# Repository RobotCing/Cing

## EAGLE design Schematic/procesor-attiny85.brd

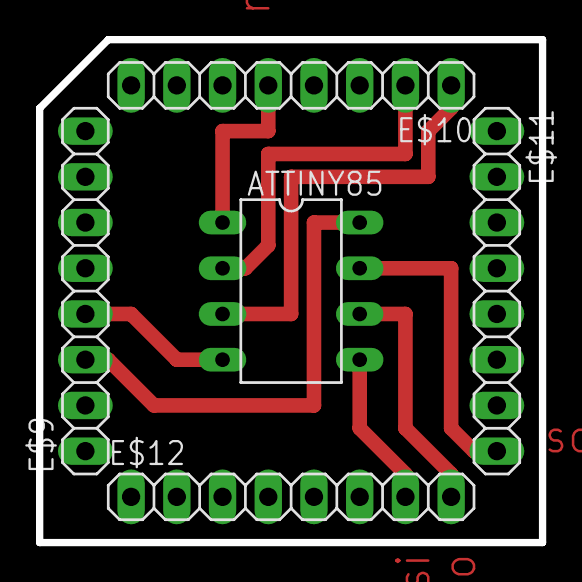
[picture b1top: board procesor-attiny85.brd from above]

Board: 2 copper layers, 27.9 x 27.9 mm, 5 parts (0 on the bottom side), 8 nets.

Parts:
ATTINY85: DIL08
E$9, E$10, E$11, E$12: 1X08

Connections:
S$2: ATTINY85.1, E$10.5
S$3: ATTINY85.4, E$9.4
S$4: ATTINY85.8, E$9.3
S$5: ATTINY85.7, E$11.8
S$6: ATTINY85.3, E$10.1
S$7: ATTINY85.2, E$10.2
S$8: ATTINY85.5, E$12.7
S$10: ATTINY85.6, E$12.8

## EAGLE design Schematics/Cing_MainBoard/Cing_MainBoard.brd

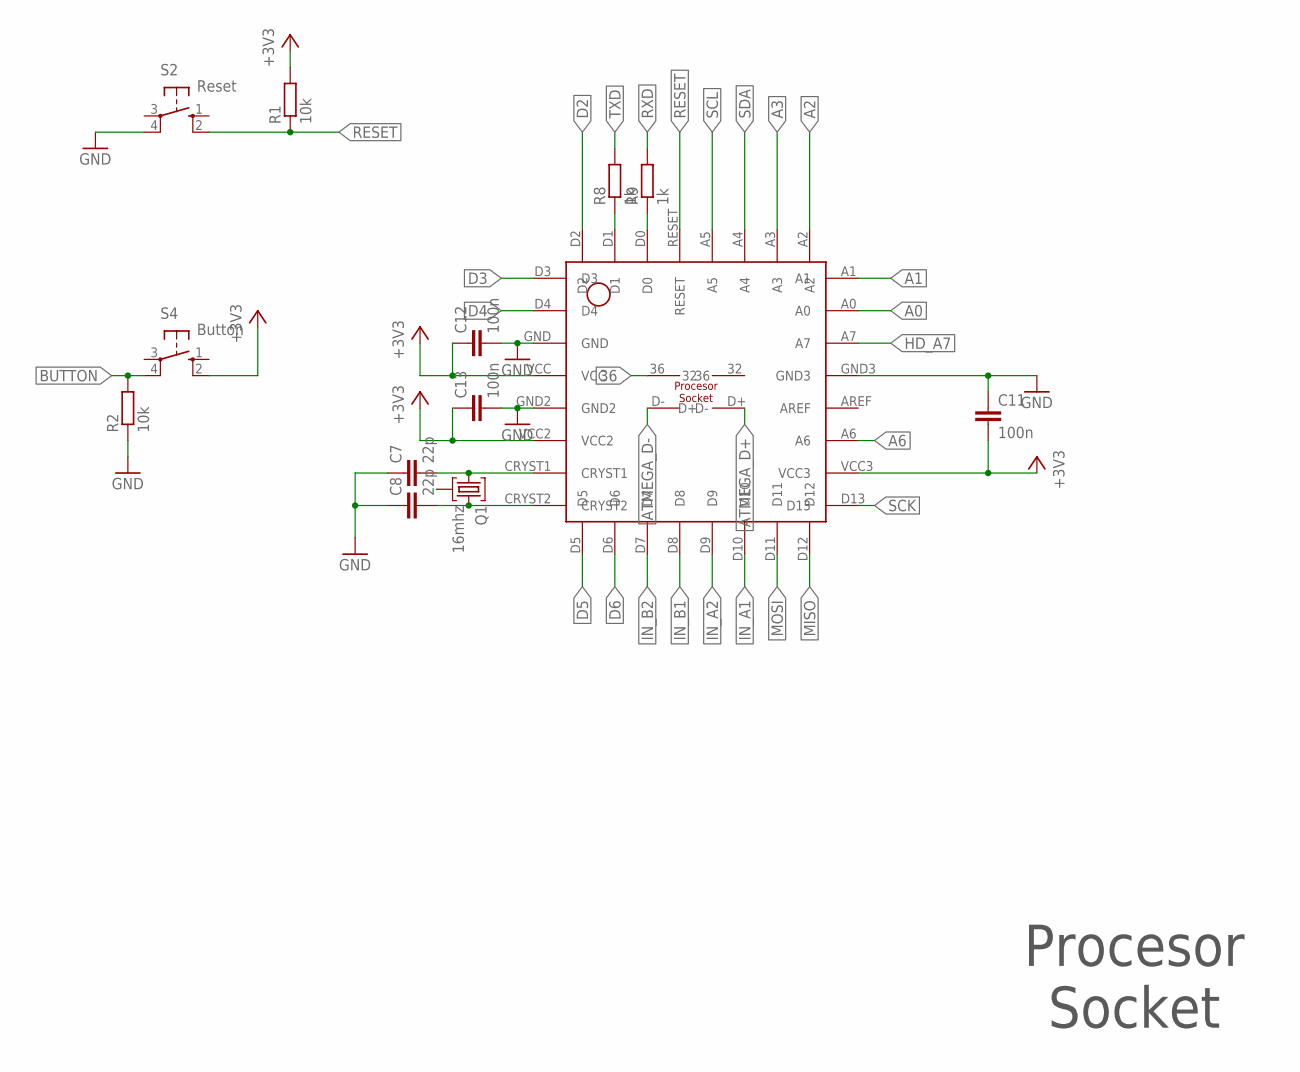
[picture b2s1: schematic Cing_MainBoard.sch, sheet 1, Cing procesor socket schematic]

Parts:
C7, C8: 22p; C1206
C11, C12, C13: 100n; C1206
Q1: 16mhz; HC49U
R1, R2: 10k; R1206
R8, R9: 1k; R1206
S2: Reset; B3F-10XX
S4: Button; B3F-10XX
U$1: PROCESSOR-SOCKET_PCB

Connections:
36: U$1.36; also elsewhere on the board
+3V3: C11.2, C12.1, C13.1, R1.2, S4.2 (S1), U$1.VCC, U$1.VCC2, U$1.VCC3; also elsewhere on the board
A0: U$1.A0; also elsewhere on the board
A1: U$1.A1; also elsewhere on the board
A2: U$1.A2; also elsewhere on the board
A3: U$1.A3; also elsewhere on the board
A6: U$1.A6; also elsewhere on the board
ATMEGA_D+: U$1.D+; also elsewhere on the board
ATMEGA_D-: U$1.D-; also elsewhere on the board
BUTTON: R2.2, S4.4 (P1); also elsewhere on the board
D2: U$1.D2; also elsewhere on the board
D3: U$1.D3; also elsewhere on the board
D4: U$1.D4; also elsewhere on the board
D5: U$1.D5; also elsewhere on the board
D6: U$1.D6; also elsewhere on the board
GND: C7.1, C8.1, C11.1, C12.2, C13.2, R2.1, S2.4 (P1), U$1.GND, U$1.GND2, U$1.GND3; also elsewhere on the board
HD_A7: U$1.A7; also elsewhere on the board
IN_A1: U$1.D10; also elsewhere on the board
IN_A2: U$1.D9; also elsewhere on the board
IN_B1: U$1.D8; also elsewhere on the board
IN_B2: U$1.D7; also elsewhere on the board
MISO: U$1.D12; also elsewhere on the board
MOSI: U$1.D11; also elsewhere on the board
unnamed: R8.1, U$1.D1
unnamed: R9.1, U$1.D0
unnamed: C8.2, Q1.3, U$1.CRYST2
unnamed: C7.2, Q1.1, U$1.CRYST1
RESET: R1.1, S2.2 (S1), U$1.RESET; also elsewhere on the board
RXD: R9.2; also elsewhere on the board
SCK: U$1.D13; also elsewhere on the board
SCL: U$1.A5; also elsewhere on the board
SDA: U$1.A4; also elsewhere on the board
TXD: R8.2; also elsewhere on the board

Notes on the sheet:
Procesor Socket

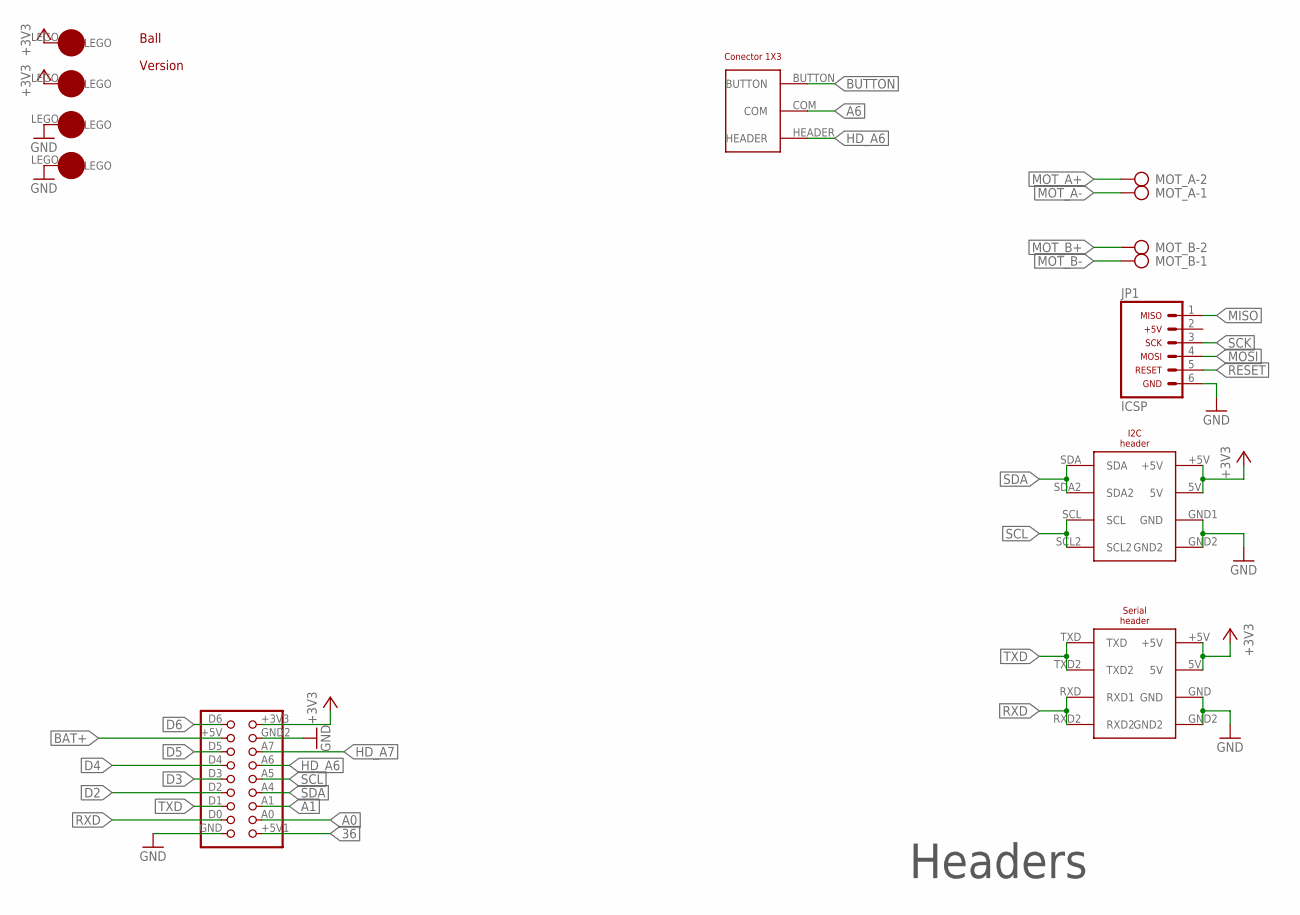
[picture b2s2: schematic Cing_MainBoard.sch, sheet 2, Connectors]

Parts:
JP1: ICSP; ICSP_HEADER
MOT_A: AK500/2
MOT_B: AK500/2
U$2: BIG_HEADER
U$3: I2C_HEADER; I2_HEADER
U$4: SERIAL_HEADER
U$15: CONNECTOR_BUTTON
U$16, U$17: 3.3V; LEGO-1X1
U$18, U$19: GND; LEGO-1X1
U$20: BALL
VERSION: 2.0; VERSION

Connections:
36: U$2.+5V1; also elsewhere on the board
+3V3: U$2.+3V3, U$3.5V, U$3.+5V, U$4.5V, U$4.+5V, U$16.LEGO, U$17.LEGO; also elsewhere on the board
A0: U$2.A0; also elsewhere on the board
A1: U$2.A1; also elsewhere on the board
A6: U$15.COM; also elsewhere on the board
BAT+: U$2.+5V; also elsewhere on the board
BUTTON: U$15.BUTTON; also elsewhere on the board
D2: U$2.D2; also elsewhere on the board
D3: U$2.D3; also elsewhere on the board
D4: U$2.D4; also elsewhere on the board
D5: U$2.D5; also elsewhere on the board
D6: U$2.D6; also elsewhere on the board
GND: JP1.6, U$2.GND, U$2.GND2 (GND1), U$3.GND1 (GND), U$3.GND2, U$4.GND, U$4.GND2, U$18.LEGO, U$19.LEGO; also elsewhere on the board
HD_A6: U$2.A6, U$15.HEADER
HD_A7: U$2.A7; also elsewhere on the board
MISO: JP1.1; also elsewhere on the board
MOSI: JP1.4; also elsewhere on the board
MOT_A+: MOT_A.2; also elsewhere on the board
MOT_A-: MOT_A.1; also elsewhere on the board
MOT_B+: MOT_B.2; also elsewhere on the board
MOT_B-: MOT_B.1; also elsewhere on the board
RESET: JP1.5; also elsewhere on the board
RXD: U$2.D0, U$4.RXD (RXD1), U$4.RXD2; also elsewhere on the board
SCK: JP1.3; also elsewhere on the board
SCL: U$2.A5, U$3.SCL, U$3.SCL2; also elsewhere on the board
SDA: U$2.A4, U$3.SDA, U$3.SDA2; also elsewhere on the board
TXD: U$2.D1, U$4.TXD, U$4.TXD2; also elsewhere on the board

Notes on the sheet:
Headers

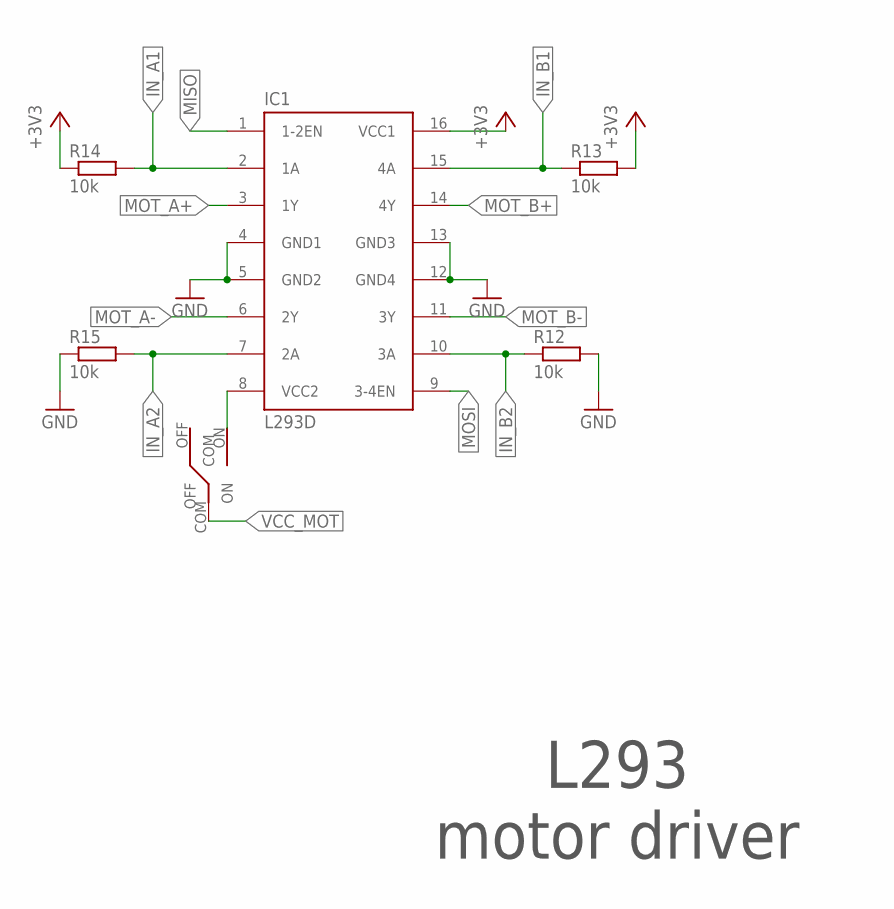
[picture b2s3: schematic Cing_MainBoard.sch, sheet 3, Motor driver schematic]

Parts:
IC1: L293D; L293
R12, R13, R14, R15: 10k; R1206
U$5: SWITCH

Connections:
+3V3: IC1.16 (VCC1), R13.2, R14.1; also elsewhere on the board
GND: IC1.4 (GND1), IC1.5 (GND2), IC1.12 (GND4), IC1.13 (GND3), R12.2, R15.1; also elsewhere on the board
IN_A1: IC1.2 (1A), R14.2; also elsewhere on the board
IN_A2: IC1.7 (2A), R15.2; also elsewhere on the board
IN_B1: IC1.15 (4A), R13.1; also elsewhere on the board
IN_B2: IC1.10 (3A), R12.1; also elsewhere on the board
MISO: IC1.1 (1-2EN); also elsewhere on the board
MOSI: IC1.9 (3-4EN); also elsewhere on the board
MOT_A+: IC1.3 (1Y); also elsewhere on the board
MOT_A-: IC1.6 (2Y); also elsewhere on the board
MOT_B+: IC1.14 (4Y); also elsewhere on the board
MOT_B-: IC1.11 (3Y); also elsewhere on the board
unnamed: IC1.8 (VCC2), U$5.ON
VCC_MOT: U$5.COM; also elsewhere on the board

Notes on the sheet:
L293 motor driver

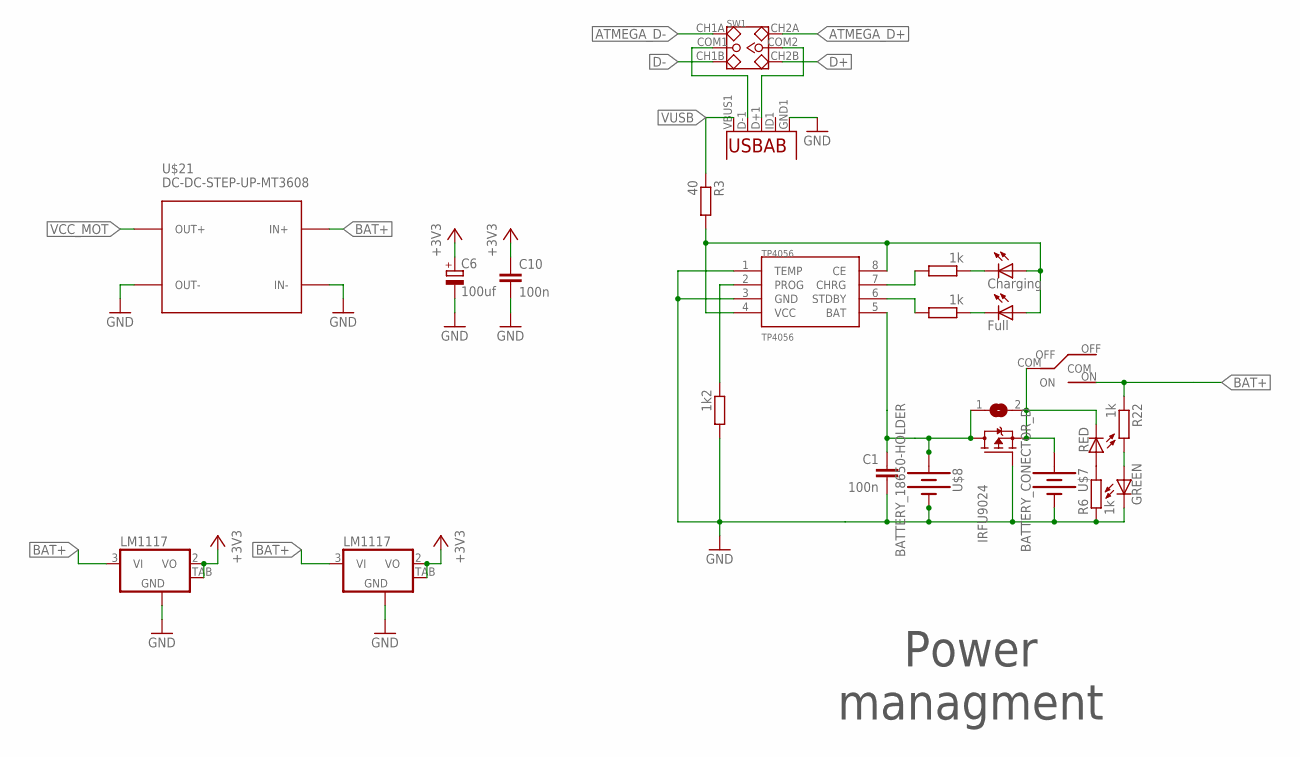
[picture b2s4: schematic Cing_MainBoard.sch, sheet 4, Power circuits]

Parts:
C1, C10: 100n; C1206
C6: 100uf; E3,5-8
IRFU9024: IRFU9024
LED1: Charging; 1206
ON: GREEN; 1206
R3: 40; R1206
R4: 1k2; R1206
R5, R6, R11, R22: 1k; R1206
REVERSE: RED; 1206
SJ1: SJ
SW1: USB_SWITCH
TP4056: TP4056
U1: MICRO_USB""; USB-MICRO-SMD
U$7: BATTERY_CONECTOR_D
U$8: BATTERY_18650-HOLDER
U$9: SWITCH
U$10, U$11: LM1117
U$21: DC-DC-STEP-UP-MT3608
YELLOW: Full; 1206

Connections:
+3V3: C6.+, C10.1, U$10.2 (VO), U$10.TAB (OUT), U$11.2 (VO), U$11.TAB (OUT); also elsewhere on the board
ATMEGA_D+: SW1.CH2A; also elsewhere on the board
ATMEGA_D-: SW1.CH1A; also elsewhere on the board
BAT+: R22.1, U$9.ON, U$10.3 (VI), U$11.3 (VI), U$21.IN+; also elsewhere on the board
D+: SW1.CH2B; also elsewhere on the board
D-: SW1.CH1B; also elsewhere on the board
GND: C1.2, C6.-, C10.2, IRFU9024.G, ON.C, R4.2, R6.1, TP4056.1 (TEMP), TP4056.3 (GND), U1.GND1 (GND), U$7.-, U$8.GND@1 (-), U$8.GND@2 (-1), U$8.GND@3 (-2), U$10.1 (GND), U$11.1 (GND), U$21.IN-, U$21.OUT-; also elsewhere on the board
IRFU: C1.1, IRFU9024.D, SJ1.1, TP4056.5 (BAT), U$8.PWR@1 (+), U$8.PWR@2 (+1), U$8.PWR@3 (+2)
unnamed: R6.2, REVERSE.A
unnamed: SW1.COM1, U1.D-1 (D-)
unnamed: LED1.C, R5.1
unnamed: SW1.COM2, U1.D+1 (D+)
unnamed: R11.1, YELLOW.C
unnamed: R11.2, TP4056.6 (STDBY)
unnamed: R5.2, TP4056.7 (CHRG)
unnamed: LED1.A, R3.2, TP4056.4 (VCC), TP4056.8 (CE), YELLOW.A
unnamed: R4.1, TP4056.2 (PROG)
unnamed: IRFU9024.S, REVERSE.C, SJ1.2, U$7.+, U$9.COM
unnamed: ON.A, R22.2
VCC_MOT: U$21.OUT+; also elsewhere on the board
VUSB: R3.1, U1.VBUS1 (VBUS); also elsewhere on the board

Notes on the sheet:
Power managment

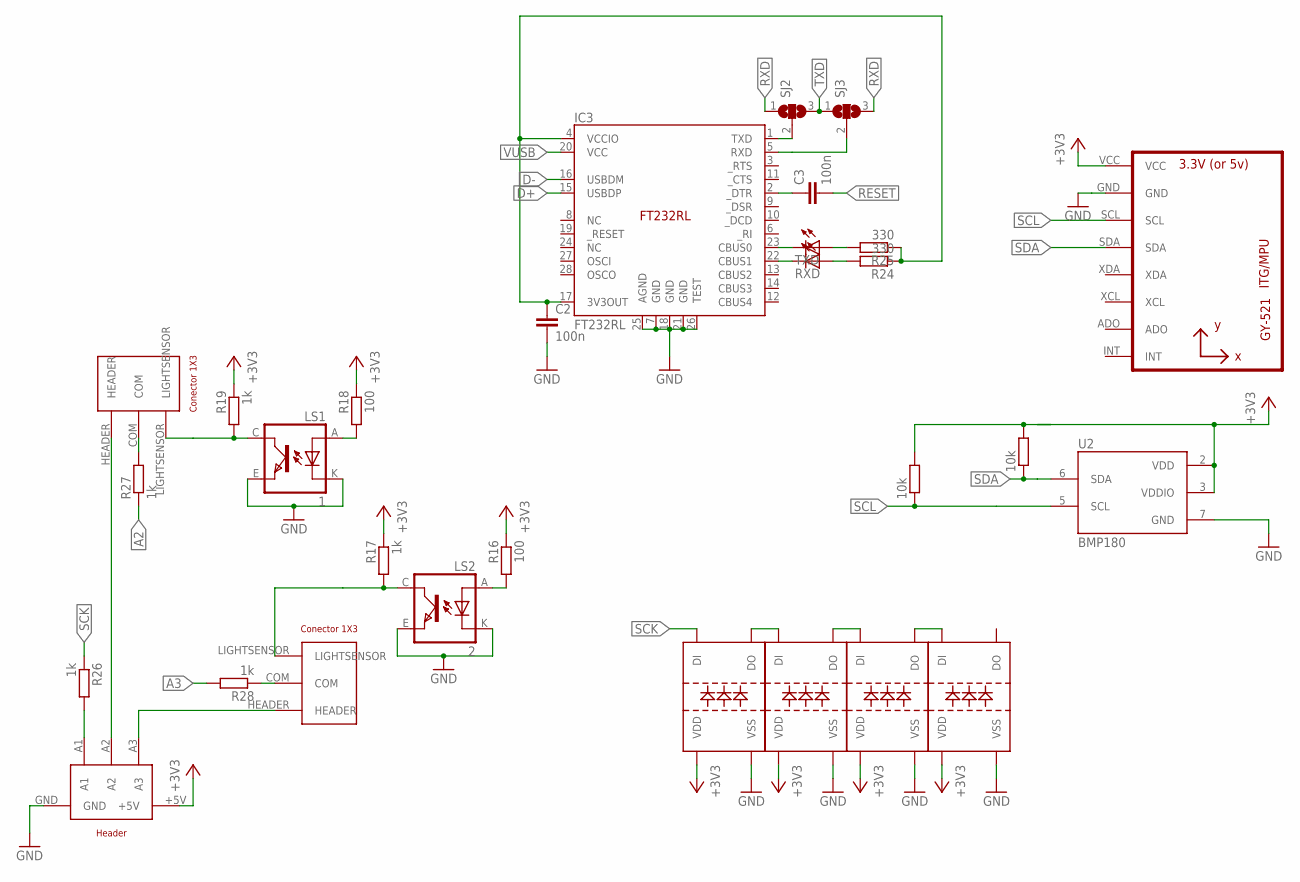
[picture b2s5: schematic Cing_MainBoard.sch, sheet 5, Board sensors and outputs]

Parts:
C2, C3: 100n; C1206
IC3: FT232RL
LED3: RXD; 1206
LED5, LED6, LED7, LED8: WS2812B
LS1: 1; TCRT5000
LS2: 2; TCRT5000
R16, R18: 100; R1206
R17, R19, R26, R27, R28: 1k; R1206
R24, R25: 330; R1206
R30, R31: 10k; R1206
SJ2, SJ3: SJ2W; SJ_2
TXD: TXD; 1206
U2: BMP180
U3: MPU-6050MPU6050; MPU-6050
U$12: CONNECTOR_1X5
U$13, U$14: CONNECTOR_LIGHT_SENSOR

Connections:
+3V3: LED5.1 (VDD), LED6.1 (VDD), LED7.1 (VDD), LED8.1 (VDD), R16.1, R17.1, R18.1, R19.1, R30.2, R31.2, U2.2 (VDD), U2.3 (VDDIO), U3.VCC, U$12.+5V; also elsewhere on the board
A2: R27.1; also elsewhere on the board
A3: R28.2; also elsewhere on the board
D+: IC3.15 (USBDP); also elsewhere on the board
D-: IC3.16 (USBDM); also elsewhere on the board
GND: C2.2, IC3.7 (GND), IC3.18 (GND), IC3.21 (GND), IC3.25 (AGND), IC3.26 (TEST), LED5.3 (VSS), LED6.3 (VSS), LED7.3 (VSS), LED8.3 (VSS), LS1.E (EMITTER), LS1.K (CATHODE), LS2.E (EMITTER), LS2.K (CATHODE), U2.7 (GND), U3.GND, U$12.GND; also elsewhere on the board
unnamed: LED5.2 (DO), LED6.4 (DI)
unnamed: LED6.2 (DO), LED7.4 (DI)
unnamed: R28.1, U$14.COM
unnamed: LED7.2 (DO), LED8.4 (DI)
unnamed: LS2.A (ANODE), R16.2
unnamed: LS1.A (ANODE), R18.2
unnamed: LS1.C (COLLECTOR), R19.2, U$13.LIGHTSENSOR
unnamed: U$12.A2, U$13.HEADER
unnamed: LED3.A, R24.2
unnamed: IC3.22 (CBUS1), LED3.C
unnamed: R25.2, TXD.A
unnamed: C3.1, IC3.2 (_DTR)
unnamed: IC3.5 (RXD), SJ3.2
unnamed: IC3.1 (TXD), SJ2.2
unnamed: C2.1, IC3.4 (VCCIO), IC3.17 (3V3OUT), R24.1, R25.1
unnamed: U$12.A3, U$14.HEADER
unnamed: R26.2, U$12.A1
unnamed: R27.2, U$13.COM
unnamed: LS2.C (COLLECTOR), R17.2, U$14.LIGHTSENSOR
RESET: C3.2; also elsewhere on the board
RXD: SJ2.1, SJ3.3; also elsewhere on the board
SCK: LED5.4 (DI), R26.1; also elsewhere on the board
SCL: R30.1, U2.5 (SCL), U3.SCL; also elsewhere on the board
SDA: R31.1, U2.6 (SDA), U3.SDA; also elsewhere on the board
T: IC3.23 (CBUS0), TXD.C
TXD: SJ2.3, SJ3.1; also elsewhere on the board
VUSB: IC3.20 (VCC); also elsewhere on the board

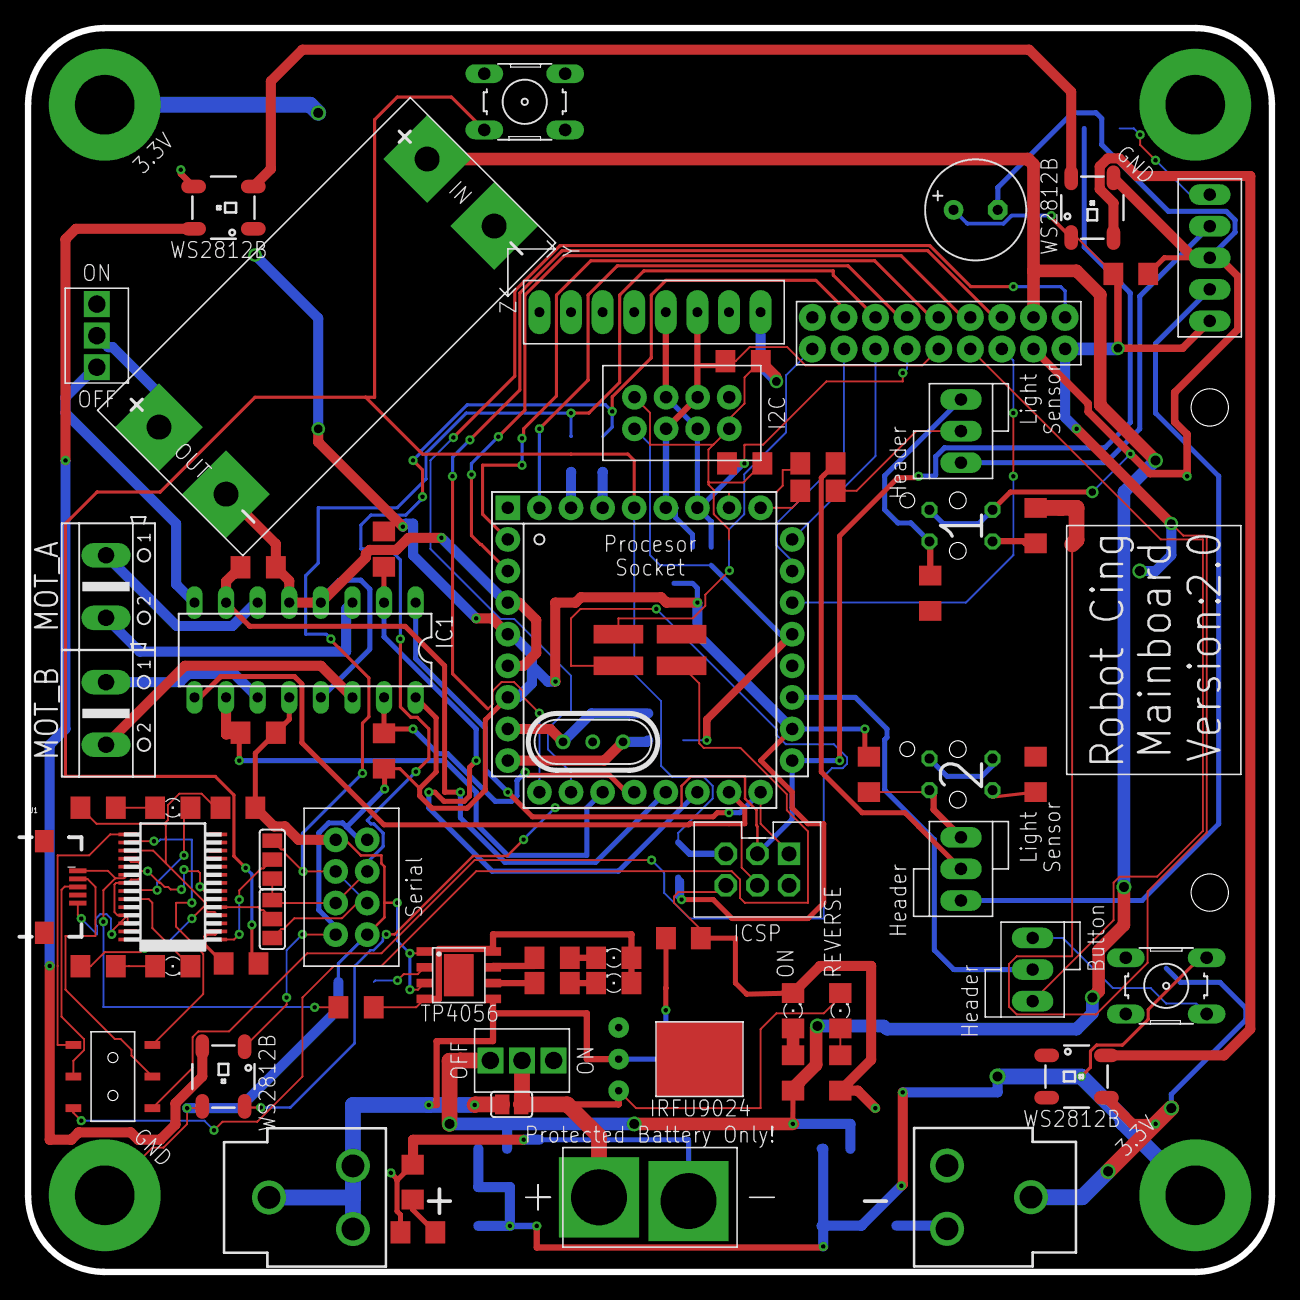
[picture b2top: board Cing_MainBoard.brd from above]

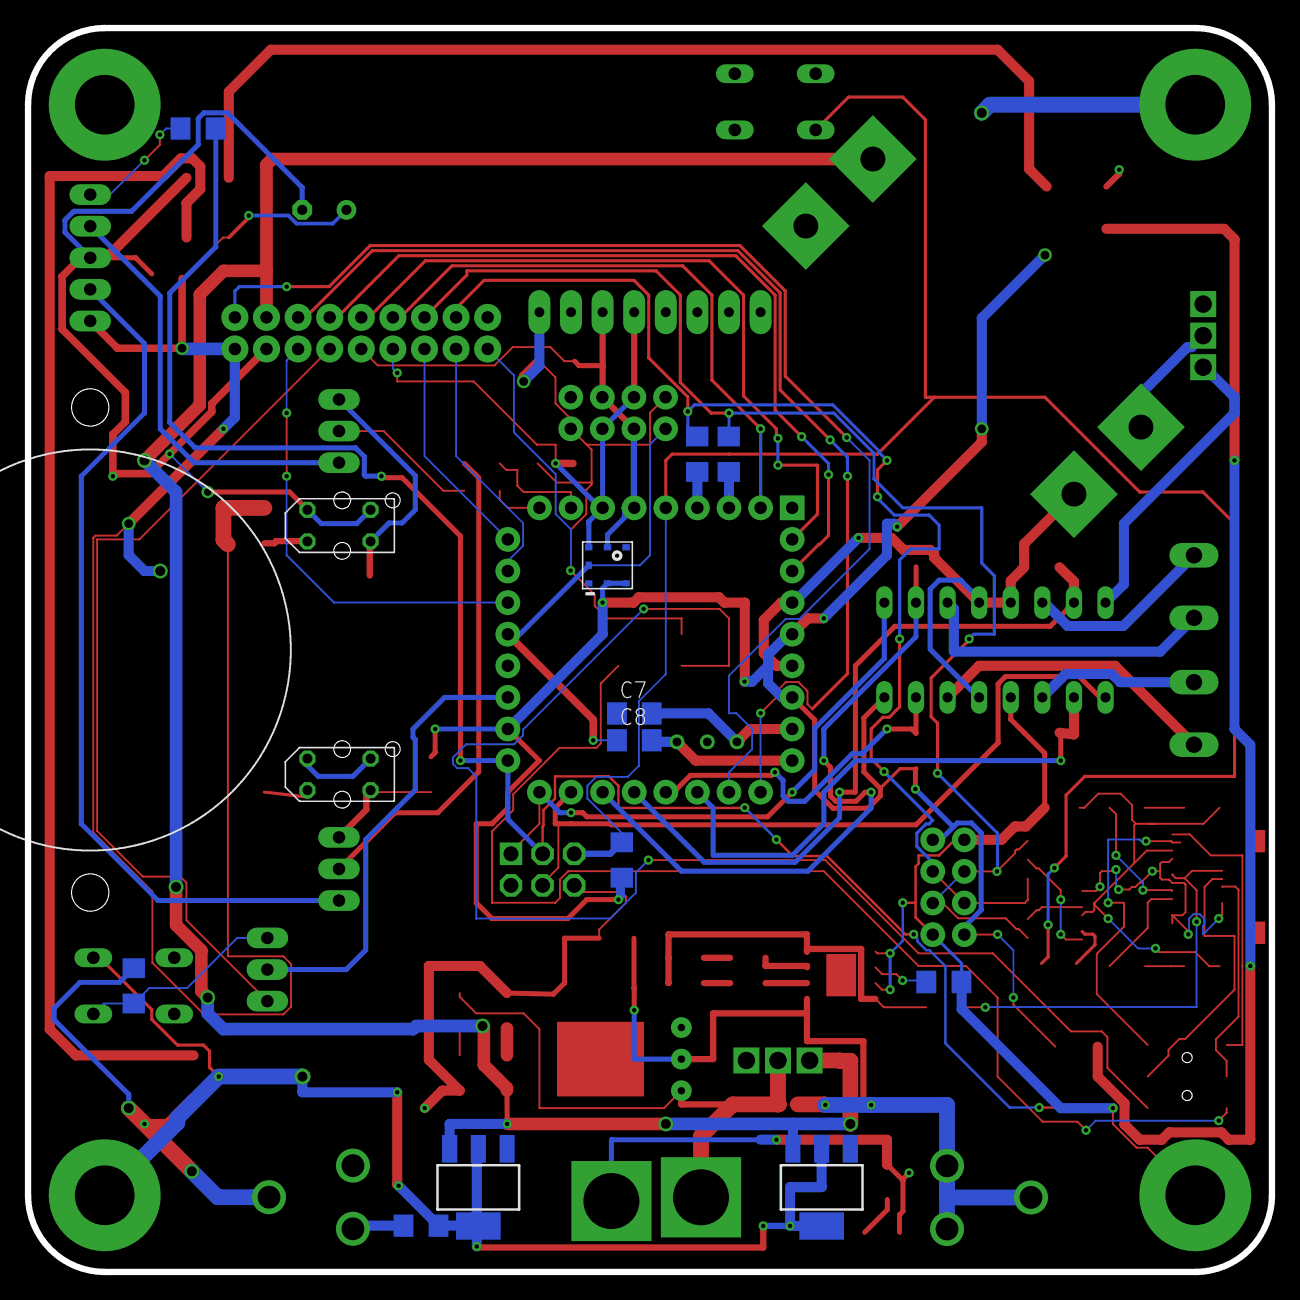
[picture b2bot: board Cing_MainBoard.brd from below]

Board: 2 copper layers, 100.0 x 100.0 mm, 85 parts (12 on the bottom side), 76 nets.

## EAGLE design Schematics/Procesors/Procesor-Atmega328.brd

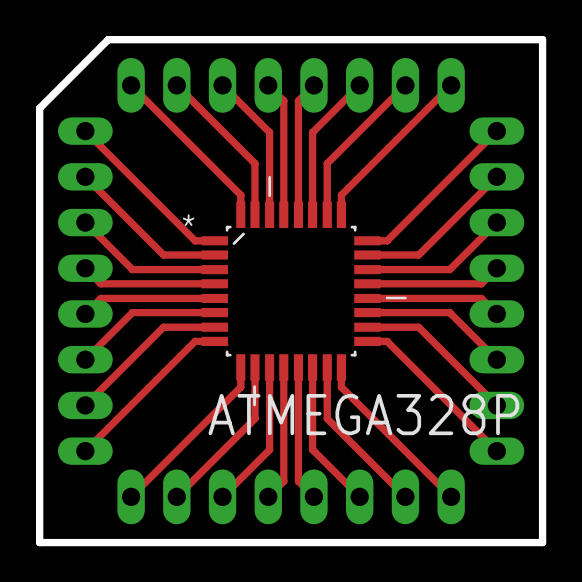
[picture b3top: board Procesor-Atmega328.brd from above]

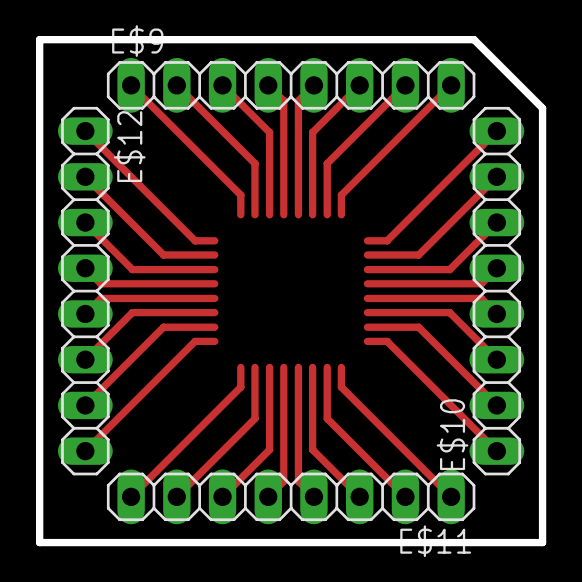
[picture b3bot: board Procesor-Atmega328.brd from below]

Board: 2 copper layers, 27.9 x 27.9 mm, 5 parts (4 on the bottom side), 32 nets.

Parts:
ATMEGA328P: QFP80P900X900X120-32N
E$9, E$10, E$11, E$12: 1X08

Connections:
S$1: ATMEGA328P.1, E$10.8
S$2: ATMEGA328P.2, E$10.7
S$3: ATMEGA328P.3, E$10.6
S$4: ATMEGA328P.4, E$10.5
S$5: ATMEGA328P.5, E$10.4
S$6: ATMEGA328P.6, E$10.3
S$7: ATMEGA328P.7, E$10.2
S$8: ATMEGA328P.8, E$10.1
S$9: ATMEGA328P.9, E$11.1
S$10: ATMEGA328P.10, E$11.2
S$11: ATMEGA328P.11, E$11.3
S$12: ATMEGA328P.12, E$11.4
S$13: ATMEGA328P.13, E$11.5
S$14: ATMEGA328P.14, E$11.6
S$15: ATMEGA328P.15, E$11.7
S$16: ATMEGA328P.16, E$11.8
S$17: ATMEGA328P.17, E$12.8
S$18: ATMEGA328P.18, E$12.7
S$19: ATMEGA328P.19, E$12.6
S$20: ATMEGA328P.20, E$12.5
S$21: ATMEGA328P.21, E$12.4
S$22: ATMEGA328P.22, E$12.3
S$23: ATMEGA328P.23, E$12.2
S$24: ATMEGA328P.24, E$12.1
S$25: ATMEGA328P.25, E$9.1
S$26: ATMEGA328P.26, E$9.2
S$27: ATMEGA328P.27, E$9.3
S$28: ATMEGA328P.28, E$9.4
S$29: ATMEGA328P.29, E$9.5
S$30: ATMEGA328P.30, E$9.6
S$31: ATMEGA328P.31, E$9.7
S$32: ATMEGA328P.32, E$9.8

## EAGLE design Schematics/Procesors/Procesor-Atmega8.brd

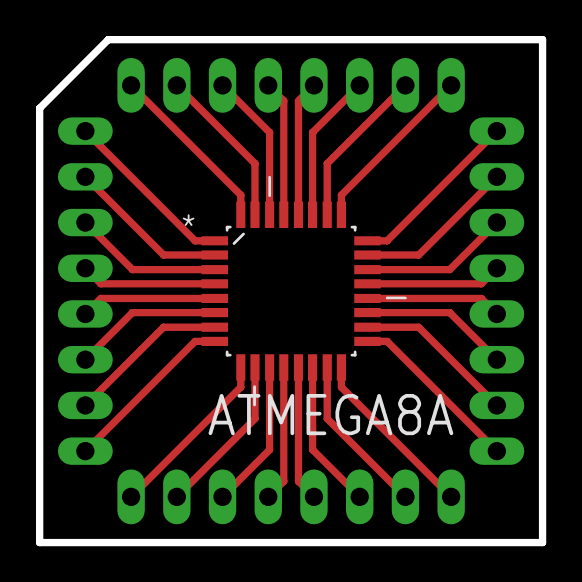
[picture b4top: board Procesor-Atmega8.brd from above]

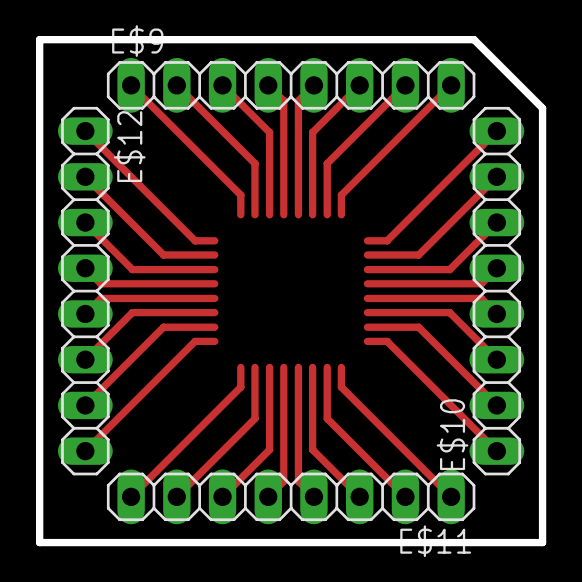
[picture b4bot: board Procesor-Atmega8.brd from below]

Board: 2 copper layers, 27.9 x 27.9 mm, 5 parts (4 on the bottom side), 32 nets.

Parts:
ATMEGA8A: QFP80P900X900X120-32N
E$9, E$10, E$11, E$12: 1X08

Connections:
S$1: ATMEGA8A.1, E$10.8
S$2: ATMEGA8A.2, E$10.7
S$3: ATMEGA8A.3, E$10.6
S$4: ATMEGA8A.4, E$10.5
S$5: ATMEGA8A.5, E$10.4
S$6: ATMEGA8A.6, E$10.3
S$7: ATMEGA8A.7, E$10.2
S$8: ATMEGA8A.8, E$10.1
S$9: ATMEGA8A.9, E$11.1
S$10: ATMEGA8A.10, E$11.2
S$11: ATMEGA8A.11, E$11.3
S$12: ATMEGA8A.12, E$11.4
S$13: ATMEGA8A.13, E$11.5
S$14: ATMEGA8A.14, E$11.6
S$15: ATMEGA8A.15, E$11.7
S$16: ATMEGA8A.16, E$11.8
S$17: ATMEGA8A.17, E$12.8
S$18: ATMEGA8A.18, E$12.7
S$19: ATMEGA8A.19, E$12.6
S$20: ATMEGA8A.20, E$12.5
S$21: ATMEGA8A.21, E$12.4
S$22: ATMEGA8A.22, E$12.3
S$23: ATMEGA8A.23, E$12.2
S$24: ATMEGA8A.24, E$12.1
S$25: ATMEGA8A.25, E$9.1
S$26: ATMEGA8A.26, E$9.2
S$27: ATMEGA8A.27, E$9.3
S$28: ATMEGA8A.28, E$9.4
S$29: ATMEGA8A.29, E$9.5
S$30: ATMEGA8A.30, E$9.6
S$31: ATMEGA8A.31, E$9.7
S$32: ATMEGA8A.32, E$9.8

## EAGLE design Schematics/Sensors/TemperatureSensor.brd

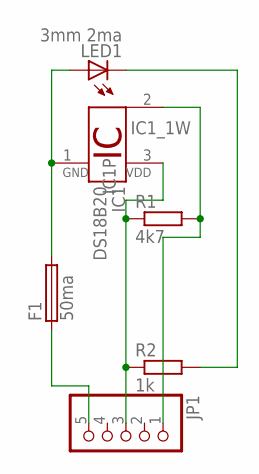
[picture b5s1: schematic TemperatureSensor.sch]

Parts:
F1: 50ma; MF-SMDF050
IC1: DS18B20; TO92-
JP1: PINHD-1X5/90; 1X05/90
LED1: 3mm 2ma; LED3MM
R1: 4k7; R1206
R2: 1k; R1206

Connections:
unnamed: F1.2, IC1.1 (GND), LED1.A
unnamed: LED1.K (C), R2.2
unnamed: IC1.2 (1W), JP1.1, R1.2
unnamed: IC1.3 (VDD), JP1.3, R1.1, R2.1
unnamed: F1.1, JP1.5

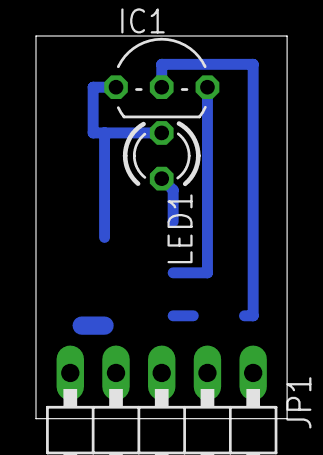
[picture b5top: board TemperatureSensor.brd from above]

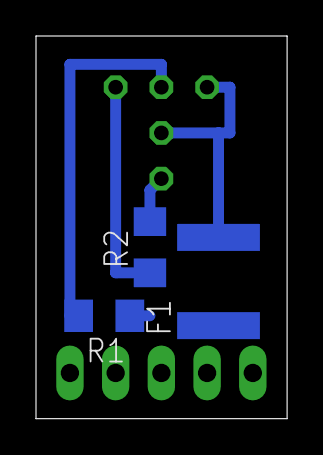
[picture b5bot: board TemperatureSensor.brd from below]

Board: 2 copper layers, 13.9 x 21.3 mm, 6 parts (3 on the bottom side), 5 nets.
